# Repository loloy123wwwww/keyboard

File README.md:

HI heres everything u need to know to find anything. 

So in FILES there are files all KiCad and 3D and firmware.                                                                                                                   
Each category has its own README.md where u can find the pictures and info.                                                                                                                
In COST of everything u can find the .bom file and all the things il need                                                                                                         
PICTURES(the file) arent important since i put all of the pictures in each category.                                                                                           
also i added better kicad file inside the kicad folder it uses a better and custom pi pico library                                                                           

Setup(if u wanna download and make ur own keyboard: 

Download Keyboard .zip file (https://github.com/loloy123wwwww/keyboard/blob/main/FILES/KiCad/keyboard.zip) or download KiCad file if u want to make changes, 
put the ready .zip file to jlpcb or any pcb manufacturer. 

buy all these: 
Diode 65x 
any mx cherry switches 65x 
Keycaps for full keyboard or 3D print them 
RP pico 2 
buy some material to solder with 

essentinals: soldering iron, 3D printer(or ask in slack for someone to 3D print for you) 

DOWN HERE I ADDED ALL THE PICTURES BUT THEY ARE IN EACH CATEGORY

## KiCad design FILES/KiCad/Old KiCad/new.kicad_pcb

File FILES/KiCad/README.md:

here u will find all of the kicad files and pictures will be here(scroll down there are more)

Explanation of each file
KiCad new: uses new rp pico library so its more accurate

KiCad old: uses basic library for rp pico mainly used if u wanna see the project(should work same but the new is more accurate)

Keyboard:   its a ready to use pcb design all packed in .zip file so it is avalible to put this file into PCB manufacturer, basiclly ready to use

heres the picture of the schematic:

and the wiring(PCB):

and the PCB in 3D viewer

and here is the little diode

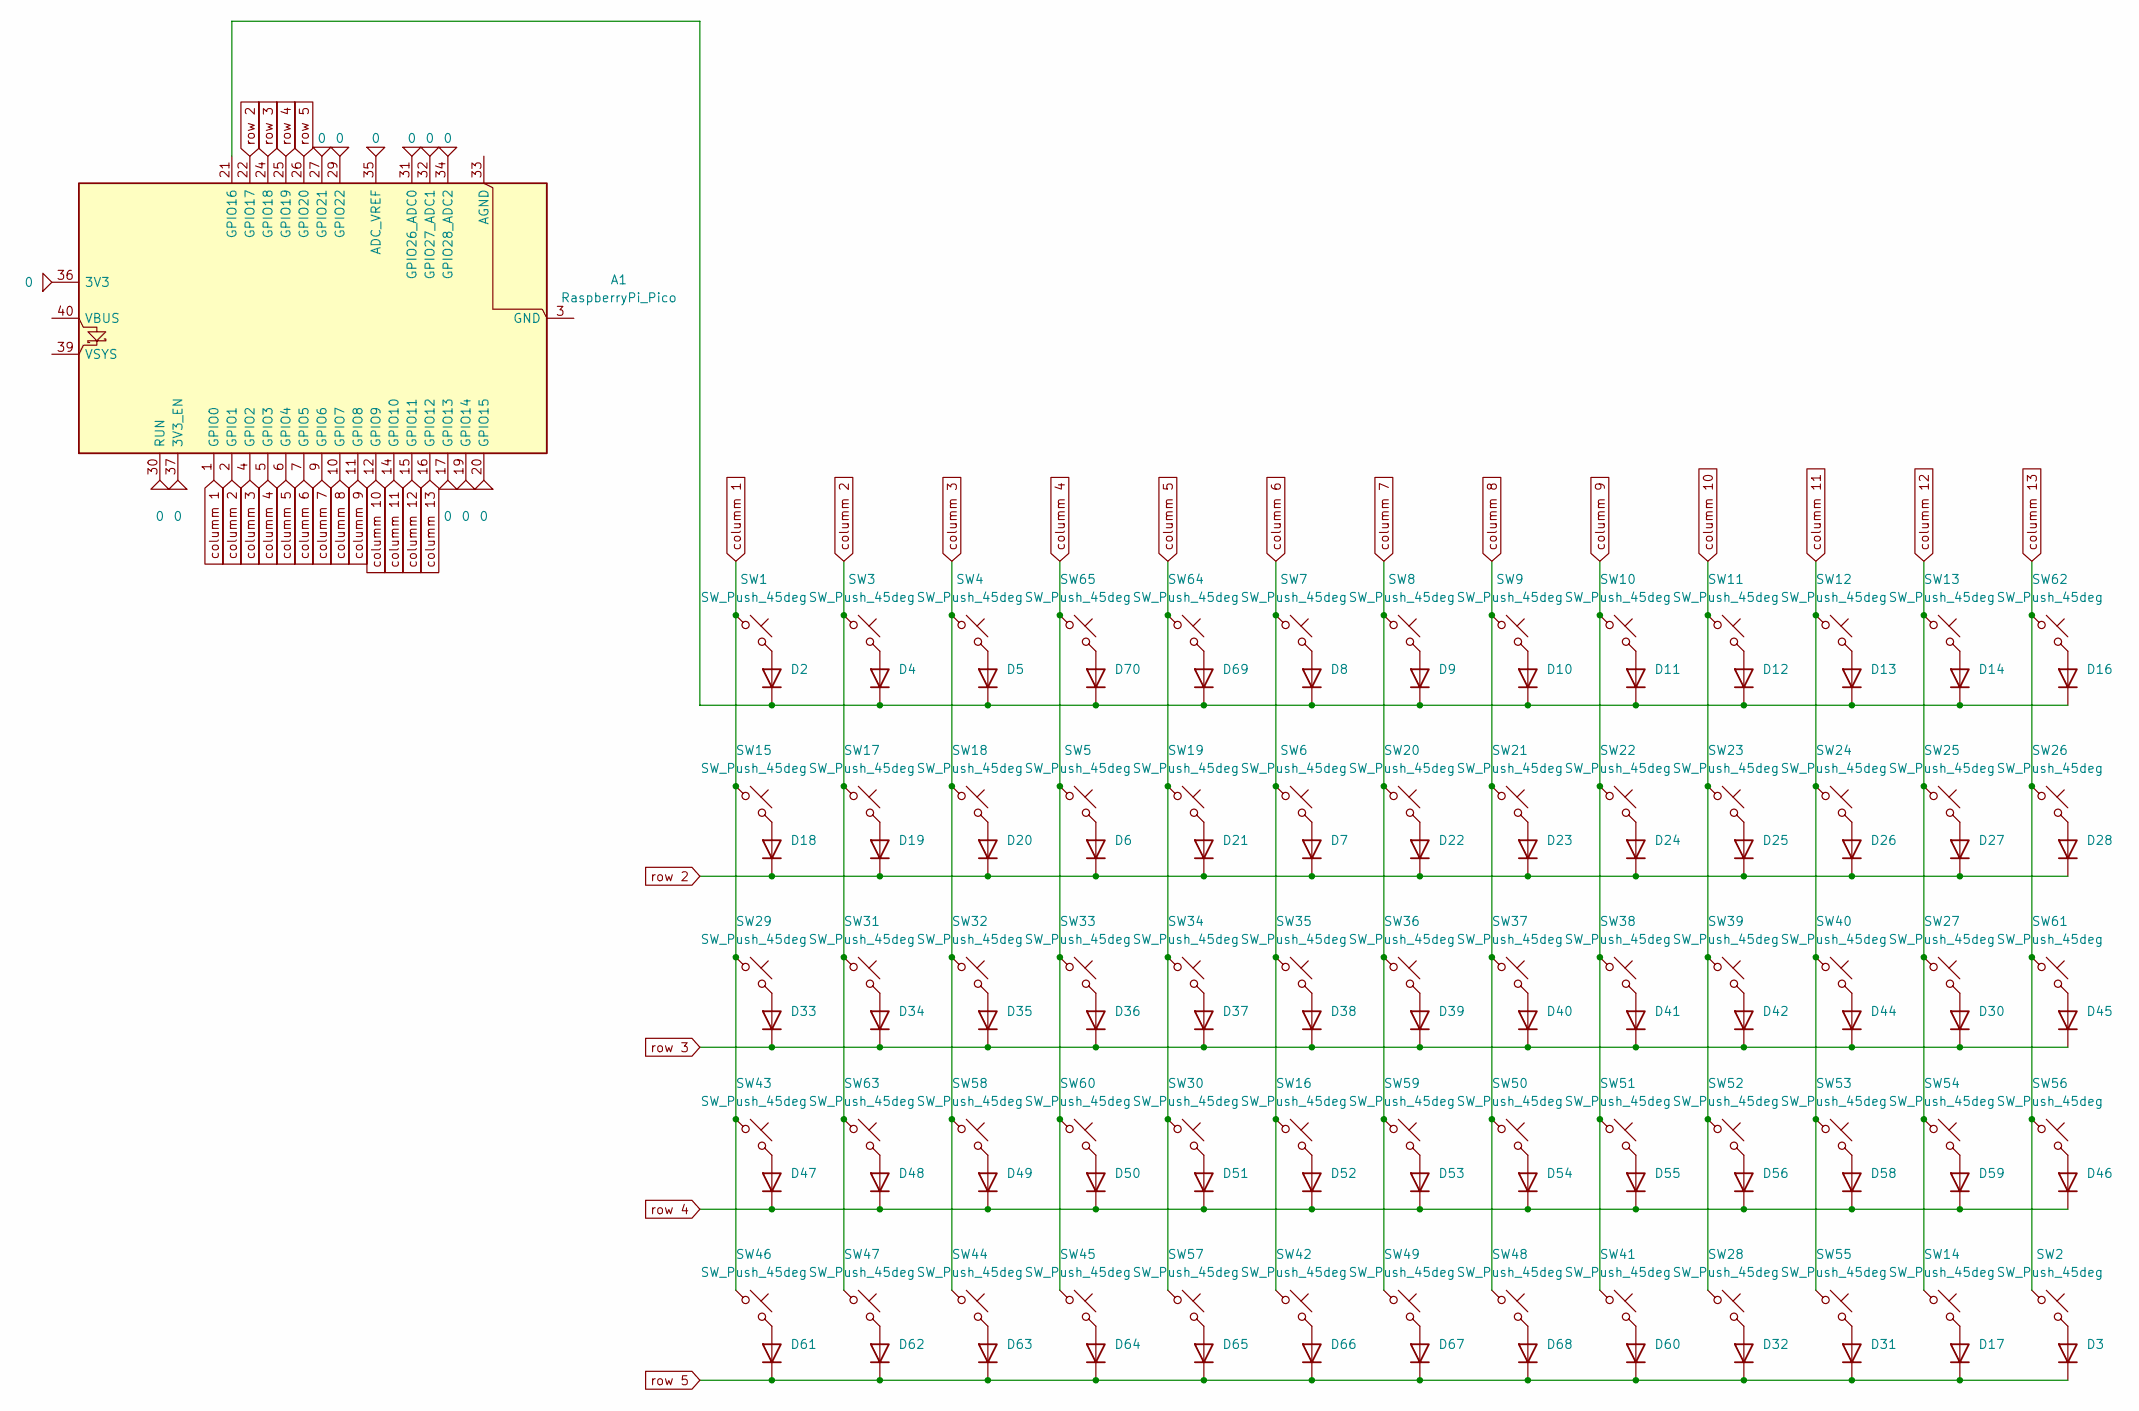
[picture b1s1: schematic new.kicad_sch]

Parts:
A1: RaspberryPi_Pico; RaspberryPi_Pico_Common_Unspecified
D2, D3, D4, D5, D6, D7, D8, D9, D10, D11, D12, D13, D14, D16, D17, D18, D19, D20, D21, D22, D23, D24, D25, D26, D27, D28, D30, D31, D32, D33, D34, D35, D36, D37, D38, D39, D40, D41, D42, D44, D45, D46, D47, D48, D49, D50, D51, D52, D53, D54, D55, D56, D58, D59, D60, D61, D62, D63, D64, D65, D66, D67, D68, D69, D70: 1N4148WT; D_SOD-523
SW1, SW2, SW3, SW4, SW5, SW6, SW7, SW8, SW9, SW10, SW11, SW12, SW13, SW16, SW17, SW18, SW19, SW20, SW21, SW22, SW23, SW24, SW25, SW26, SW27, SW30, SW31, SW32, SW33, SW34, SW35, SW36, SW37, SW38, SW39, SW40, SW50, SW51, SW52, SW53, SW54, SW55, SW56, SW58, SW59, SW60, SW61, SW62, SW63, SW64, SW65: SW_Push_45deg; SW_Cherry_MX_1.00u_PCB
SW14: SW_Push_45deg; SW_Cherry_MX_2.00u_PCB
SW15: SW_Push_45deg; SW_Cherry_MX_1.50u_PCB
SW28: SW_Push_45deg; SW_Cherry_MX_ISOEnter_PCB
SW29: SW_Push_45deg; SW_Cherry_MX_1.75u_PCB
SW41: SW_Push_45deg; SW_Cherry_MX_2.75u_PCB
SW42, SW43, SW44, SW46, SW47, SW48, SW49, SW57: SW_Push_45deg; SW_Cherry_MX_1.25u_PCB
SW45: SW_Push_45deg; SW_Cherry_MX_6.25u_PCB

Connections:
unnamed 0: A1.3 (GND), A1.8 (GND), A1.13 (GND), A1.18 (GND), A1.23 (GND), A1.28 (GND), A1.38 (GND); also elsewhere on the board
unnamed: A1.21 (GPIO16), D2.1 (K), D4.1 (K), D5.1 (K), D8.1 (K), D9.1 (K), D10.1 (K), D11.1 (K), D12.1 (K), D13.1 (K), D14.1 (K), D16.1 (K), D69.1 (K), D70.1 (K)
unnamed 2: A1.39 (VSYS); also elsewhere on the board
unnamed: D2.2 (A), SW1.2
unnamed: D3.2 (A), SW2.2
unnamed: D4.2 (A), SW3.2
unnamed: D5.2 (A), SW4.2
unnamed: D6.2 (A), SW5.2
unnamed: D7.2 (A), SW6.2
unnamed: D8.2 (A), SW7.2
unnamed: D9.2 (A), SW8.2
unnamed: D10.2 (A), SW9.2
unnamed: D11.2 (A), SW10.2
unnamed: D12.2 (A), SW11.2
unnamed: D13.2 (A), SW12.2
unnamed: D14.2 (A), SW13.2
unnamed: D16.2 (A), SW62.2
unnamed: D17.2 (A), SW14.2
unnamed: D18.2 (A), SW15.2
unnamed: D19.2 (A), SW17.2
unnamed: D20.2 (A), SW18.2
unnamed: D21.2 (A), SW19.2
unnamed: D22.2 (A), SW20.2
unnamed: D23.2 (A), SW21.2
unnamed: D24.2 (A), SW22.2
unnamed: D25.2 (A), SW23.2
unnamed: D26.2 (A), SW24.2
unnamed: D27.2 (A), SW25.2
unnamed: D28.2 (A), SW26.2
unnamed: D30.2 (A), SW27.2
unnamed: D31.2 (A), SW55.2
unnamed: D32.2 (A), SW28.2
unnamed: D33.2 (A), SW29.2
unnamed: D34.2 (A), SW31.2
unnamed: D35.2 (A), SW32.2
unnamed: D36.2 (A), SW33.2
unnamed: D37.2 (A), SW34.2
unnamed: D38.2 (A), SW35.2
unnamed: D39.2 (A), SW36.2
unnamed: D40.2 (A), SW37.2
unnamed: D41.2 (A), SW38.2
unnamed: D42.2 (A), SW39.2
unnamed: D44.2 (A), SW40.2
unnamed: D45.2 (A), SW61.2
unnamed: D46.2 (A), SW56.2
unnamed: D47.2 (A), SW43.2
unnamed: D48.2 (A), SW63.2
unnamed: D49.2 (A), SW58.2
unnamed: D50.2 (A), SW60.2
unnamed: D51.2 (A), SW30.2
unnamed: D52.2 (A), SW16.2
unnamed: D53.2 (A), SW59.2
unnamed: D54.2 (A), SW50.2
unnamed: D55.2 (A), SW51.2
unnamed: D56.2 (A), SW52.2
unnamed: D58.2 (A), SW53.2
unnamed: D59.2 (A), SW54.2
unnamed: D60.2 (A), SW41.2
unnamed: D61.2 (A), SW46.2
unnamed: D62.2 (A), SW47.2
unnamed: D63.2 (A), SW44.2
unnamed: D64.2 (A), SW45.2
unnamed: D65.2 (A), SW57.2
unnamed: D66.2 (A), SW42.2
unnamed: D67.2 (A), SW49.2
unnamed: D68.2 (A), SW48.2
unnamed: D69.2 (A), SW64.2
unnamed: D70.2 (A), SW65.2
columm 1: A1.1 (GPIO0), SW1.1, SW15.1, SW29.1, SW43.1, SW46.1
columm 2: A1.2 (GPIO1), SW3.1, SW17.1, SW31.1, SW47.1, SW63.1
columm 3: A1.4 (GPIO2), SW4.1, SW18.1, SW32.1, SW44.1, SW58.1
columm 4: A1.5 (GPIO3), SW5.1, SW33.1, SW45.1, SW60.1, SW65.1
columm 5: A1.6 (GPIO4), SW19.1, SW30.1, SW34.1, SW57.1, SW64.1
columm 6: A1.7 (GPIO5), SW6.1, SW7.1, SW16.1, SW35.1, SW42.1
columm 7: A1.9 (GPIO6), SW8.1, SW20.1, SW36.1, SW49.1, SW59.1
columm 8: A1.10 (GPIO7), SW9.1, SW21.1, SW37.1, SW48.1, SW50.1
columm 9: A1.11 (GPIO8), SW10.1, SW22.1, SW38.1, SW41.1, SW51.1
columm 10: A1.12 (GPIO9), SW11.1, SW23.1, SW28.1, SW39.1, SW52.1
columm 11: A1.14 (GPIO10), SW12.1, SW24.1, SW40.1, SW53.1, SW55.1
columm 12: A1.15 (GPIO11), SW13.1, SW14.1, SW25.1, SW27.1, SW54.1
columm 13: A1.16 (GPIO12), SW2.1, SW26.1, SW56.1, SW61.1, SW62.1
row 2: A1.22 (GPIO17), D6.1 (K), D7.1 (K), D18.1 (K), D19.1 (K), D20.1 (K), D21.1 (K), D22.1 (K), D23.1 (K), D24.1 (K), D25.1 (K), D26.1 (K), D27.1 (K), D28.1 (K)
row 3: A1.24 (GPIO18), D30.1 (K), D33.1 (K), D34.1 (K), D35.1 (K), D36.1 (K), D37.1 (K), D38.1 (K), D39.1 (K), D40.1 (K), D41.1 (K), D42.1 (K), D44.1 (K), D45.1 (K)
row 4: A1.25 (GPIO19), D46.1 (K), D47.1 (K), D48.1 (K), D49.1 (K), D50.1 (K), D51.1 (K), D52.1 (K), D53.1 (K), D54.1 (K), D55.1 (K), D56.1 (K), D58.1 (K), D59.1 (K)
row 5: A1.26 (GPIO20), D3.1 (K), D17.1 (K), D31.1 (K), D32.1 (K), D60.1 (K), D61.1 (K), D62.1 (K), D63.1 (K), D64.1 (K), D65.1 (K), D66.1 (K), D67.1 (K), D68.1 (K)

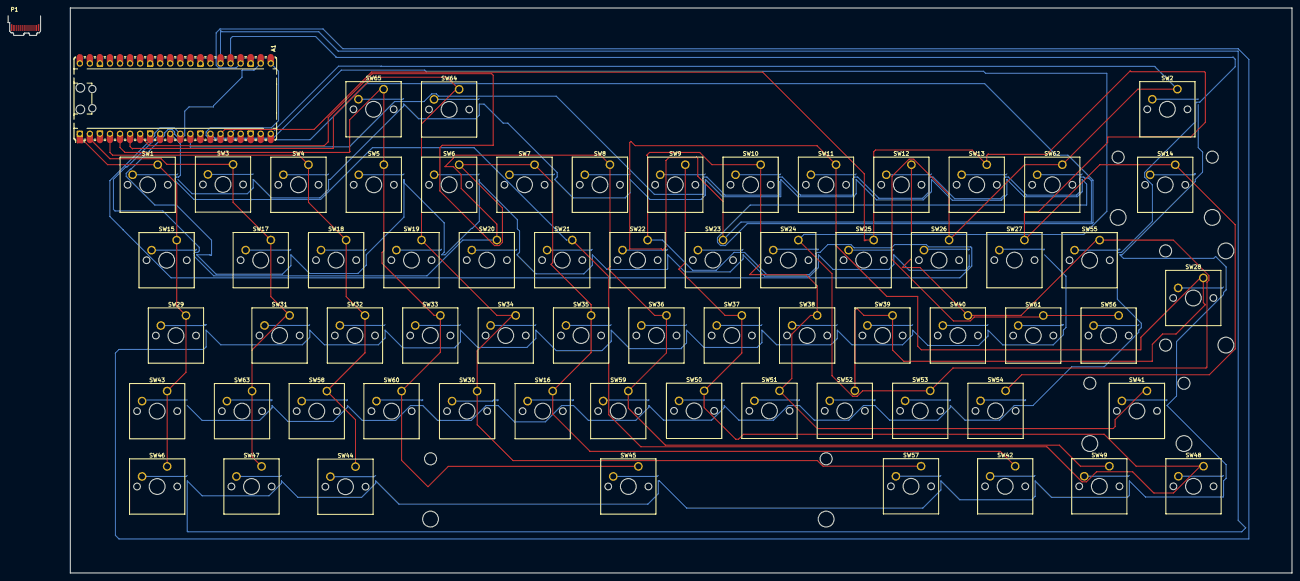
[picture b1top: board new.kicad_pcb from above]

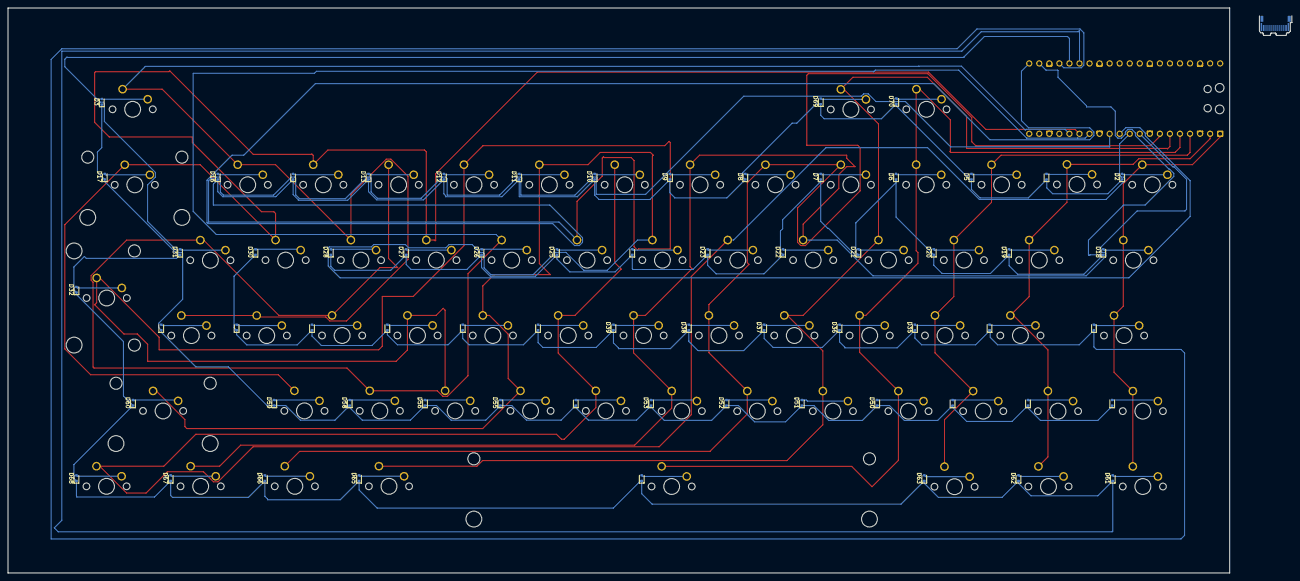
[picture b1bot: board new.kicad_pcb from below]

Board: 2 copper layers, 324.5 x 142.8 mm, 132 parts (65 on the bottom side), 85 nets.

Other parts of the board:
P1: USB_C_Plug_USB2.0; USB_C_Plug_JAE_DX07P024AJ1

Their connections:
unnamed 0: P1.A1 (GND), P1.A12 (GND), P1.B1 (GND), P1.B12 (GND); also elsewhere on the board
unnamed 2: P1.A4 (VBUS), P1.A9 (VBUS), P1.B4 (VBUS), P1.B9 (VBUS); also elsewhere on the board

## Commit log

2025-12-16 added .bom file
2025-12-16 added all KiCad files
2025-12-16 added top and bottom parts in .stl format
2025-12-16 added files
2025-12-16 Create README:md
2025-12-16 Create pictures
2025-12-16 added photos
2025-12-16 Create Firmware
2025-12-17 added all the files
2025-12-18 rename to BOM
2026-03-06 updated KiCad files
2026-03-06 Update README with file explanations
2026-03-06 updated README with setup info
2026-03-06 Revise README.md for better clarity and structure
2026-03-06 Updated README.md
    Updated README.md for clarity and added details about files and setup instructions.
